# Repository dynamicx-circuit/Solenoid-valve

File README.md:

# 这是GPIO-电磁阀驱动板
旧方案已废弃，在new分支中，改用lm5060驱动，方便了焊接，还加上了光耦隔离和防浪涌

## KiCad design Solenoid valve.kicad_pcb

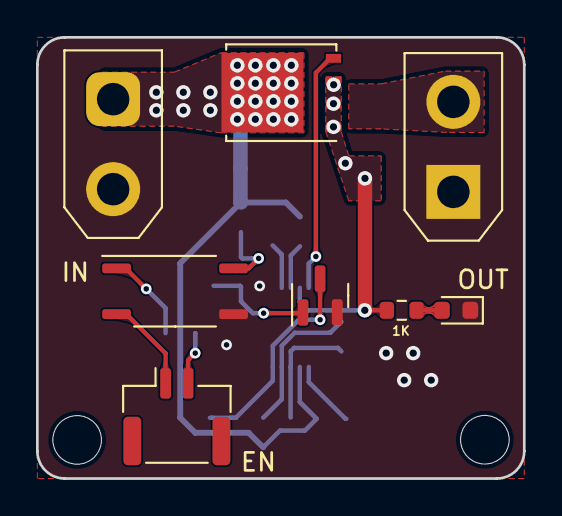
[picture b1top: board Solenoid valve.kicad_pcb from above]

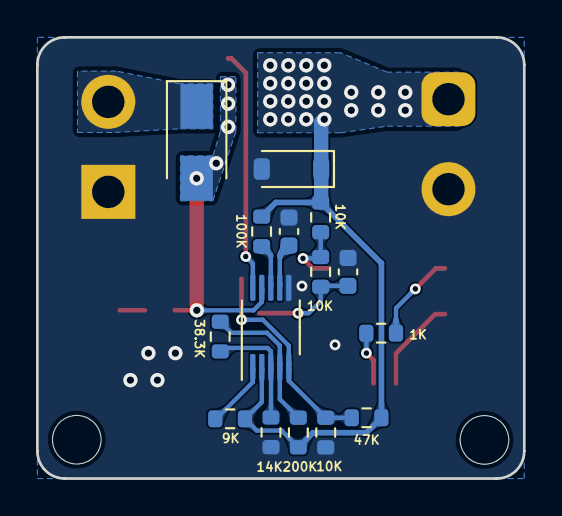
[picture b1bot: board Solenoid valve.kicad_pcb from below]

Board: 2 copper layers, 27.1 x 24.5 mm, 25 parts (15 on the bottom side), 17 nets.

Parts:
C1, C2: 100n; C_0603_1608Metric
D1: LED; LED_0603_1608Metric
D2: SS34A; D_SMA
D4: 24V; D_SOD-123
H1, H2: MountingHole; MountingHole_2.7mm_M2.5
J1: Conn_01x02; JST_GH_SM02B-GHS-TB_1x02-1MP_P1.25mm_Horizontal
J2: Conn_01x02; AMASS_XT30UPB-F_1x02_P5.0mm_Vertical
J3: Conn_01x02; AMASS_XT30UPB-M_1x02_P5.0mm_Vertical
Q1: 8050; SOT-23
Q2: CSD18540Q5B; TDSON-8-1
R1, R2, R5: 10K; R_0603_1608Metric
R4: 47K; R_0603_1608Metric
R6: 14K; R_0603_1608Metric
R7: 38.3K; R_0603_1608Metric
R8: 200K; R_0603_1608Metric
R9: 100K; R_0603_1608Metric
R10: 9K; R_0603_1608Metric
R11, R12: 1K; R_0603_1608Metric
U1: EL357N; SOIC-4_4.55x3.7mm_P2.54mm
U2: LM5060; VSSOP-10_3x3mm_P0.5mm

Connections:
+24V: D4.1 (K), J3.1, Q2.5 (D), R1.2, R4.2, R8.2, R9.2, R10.1, U2.2 (Vin)
GND: C1.2, C2.2, D1.1 (K), D4.2 (A), J2.1 (Pin_2), J3.2, Q1.2 (Emitter), R5.1, R6.1, U1.3, U2.6 (GND)
unnamed: D1.2 (A), R11.1
unnamed: D2.2 (A), Q2.1 (S), Q2.2 (S), Q2.3 (S), R11.2, U2.9 (OUT)
unnamed: D2.1 (K), J2.2 (Pin_1)
unnamed: J1.1, U1.2
unnamed: J1.2, R12.2
unnamed: C1.1, Q1.1 (Base), R2.1
unnamed: Q1.3 (Collector), R4.1, R5.2, U2.5 (EN)
unnamed: Q2.4 (G), U2.10 (GATE)
unnamed: R1.1, R2.2, U1.4
unnamed: R12.1, U1.1
unnamed: R6.2, R7.2, U2.3 (OVP)
unnamed: R10.2, U2.1 (SENSE)
unnamed: C2.1, U2.7 (TIMER)
unnamed: R7.1, R8.1, U2.4 (UVLO)
unnamed: R9.1, U2.8 (nPGD)

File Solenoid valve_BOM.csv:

"Comment","Description","Designator","Footprint","LibRef","Pins","Quantity","PartNumber","url",
"LED","desc","D1,","LED_0603_1608Metric","libref","2","1","","",
"Conn_01x02","desc","J1,","JST_GH_SM02B-GHS-TB_1x02-1MP_P1.25mm_Horizontal","libref","4","1","","",
"8050","desc","Q1,","SOT-23","libref","3","1","","",
"CSD18540Q5B","desc","Q2,","TDSON-8-1","libref","14","1","","",
"1K","desc","R11,","R_0603_1608Metric","libref","2","1","","",
"EL357N","desc","U1,","SOIC-4_4.55x3.7mm_P2.54mm","libref","4","1","","",
"100n","desc","C1,C2,","C_0603_1608Metric","libref","2","2","","",
"SS34A","desc","D2,","D_SMA","libref","2","1","","",
"10K","desc","R1,R2,R5,","R_0603_1608Metric","libref","2","3","","",
"47K","desc","R4,","R_0603_1608Metric","libref","2","1","","",
"14K","desc","R6,","R_0603_1608Metric","libref","2","1","","",
"38.3K","desc","R7,","R_0603_1608Metric","libref","2","1","","",
"200K","desc","R8,","R_0603_1608Metric","libref","2","1","","",
"100K","desc","R9,","R_0603_1608Metric","libref","2","1","","",
"9K","desc","R10,","R_0603_1608Metric","libref","2","1","","",
"1K","desc","R12,","R_0603_1608Metric","libref","2","1","","",
"LM5060","desc","U2,","VSSOP-10_3x3mm_P0.5mm","libref","10","1","","",
"Through Hole Items ",
"MountingHole","desc","H1,H2,","MountingHole_2.7mm_M2.5","libref","1","2","","",
"Conn_01x02","desc","J2,","AMASS_XT30UPB-F_1x02_P5.0mm_Vertical","libref","2","1","","",
"Conn_01x02","desc","J3,","AMASS_XT30UPB-M_1x02_P5.0mm_Vertical","libref","2","1","","",

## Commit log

2022-09-01 Change some routings
2022-10-06 Change some routings and S8050's footprint
2022-11-02 Change somes' positions and add mask
2023-02-24 Adjustment for full version
2023-02-24 Add gitinore
2023-02-26 Add protectionfor EN
2023-03-26 Add protection for OUT
2023-03-26 Add teardrops
2023-04-26 Add a mimic ss34a on the top
2023-07-17 Add a 24V voltage regulator diode
